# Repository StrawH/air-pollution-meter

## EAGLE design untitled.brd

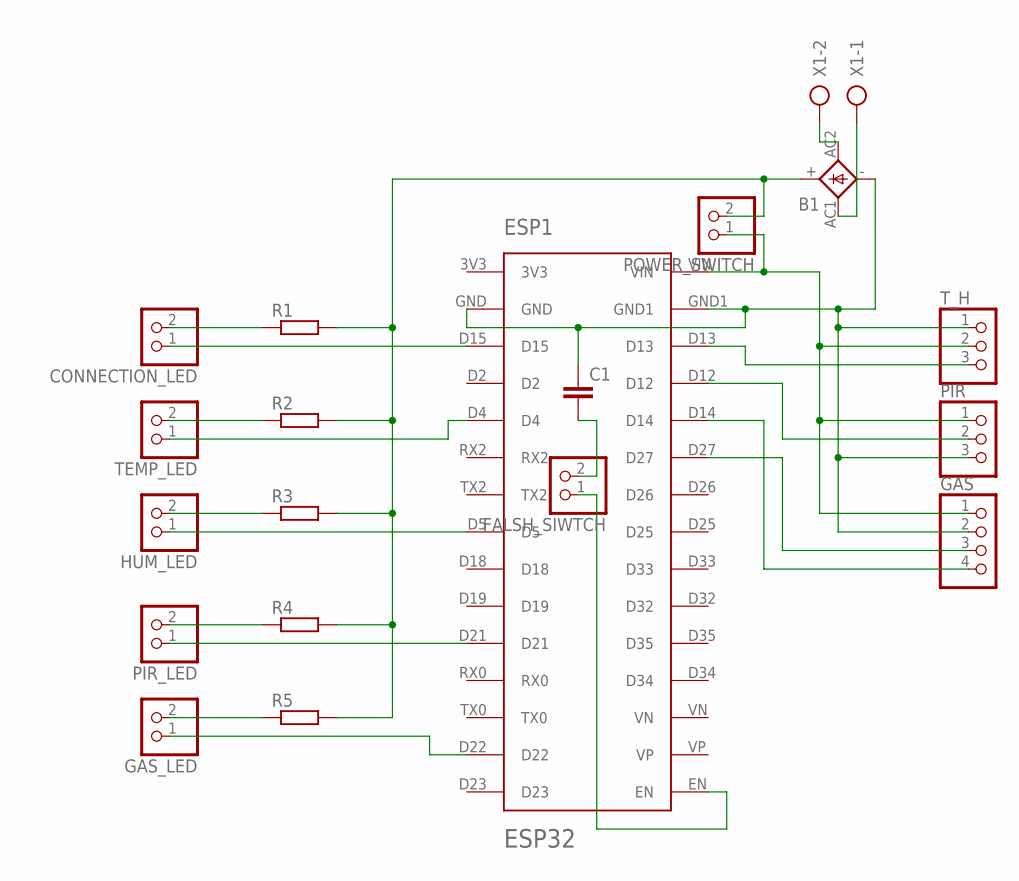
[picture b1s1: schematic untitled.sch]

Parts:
B1: 2KBB-R
C1: C5/2.5; C5B2.5
CONNECTION_LED: PINHD-1X2; 1X02
ESP1: ESP32; ESP-32
FALSH_SIWTCH: PINHD-1X2; 1X02
GAS: PINHD-1X4; 1X04
GAS_LED: PINHD-1X2; 1X02
HUM_LED: PINHD-1X2; 1X02
PIR: PINHD-1X3; 1X03
PIR_LED: PINHD-1X2; 1X02
POWER_SWITCH: PINHD-1X2; 1X02
R1, R2, R3, R4, R5: R-EU_0207/10; 0207/10
TEMP_LED: PINHD-1X2; 1X02
T_H: PINHD-1X3; 1X03
X1: AK300/2

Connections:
unnamed: B1.AC2, X1.2
unnamed: ESP1.D13, T_H.3
unnamed: ESP1.D12, PIR.2
unnamed: ESP1.D27, GAS.3
unnamed: ESP1.D14, GAS.4
unnamed: B1.-, C1.1, ESP1.GND, ESP1.GND1, GAS.2, PIR.3, T_H.1
unnamed: B1.AC1, X1.1
unnamed: B1.+, POWER_SWITCH.2, R1.2, R2.2, R3.2, R4.2, R5.2
unnamed: CONNECTION_LED.1, ESP1.D15
unnamed: ESP1.D4, TEMP_LED.1
unnamed: ESP1.D5, HUM_LED.1
unnamed: ESP1.D21, PIR_LED.1
unnamed: ESP1.D22, GAS_LED.1
unnamed: GAS_LED.2, R5.1
unnamed: PIR_LED.2, R4.1
unnamed: HUM_LED.2, R3.1
unnamed: R2.1, TEMP_LED.2
unnamed: CONNECTION_LED.2, R1.1
unnamed: ESP1.VIN, GAS.1, PIR.1, POWER_SWITCH.1, T_H.2
unnamed: C1.2, FALSH_SIWTCH.2
unnamed: ESP1.EN, FALSH_SIWTCH.1

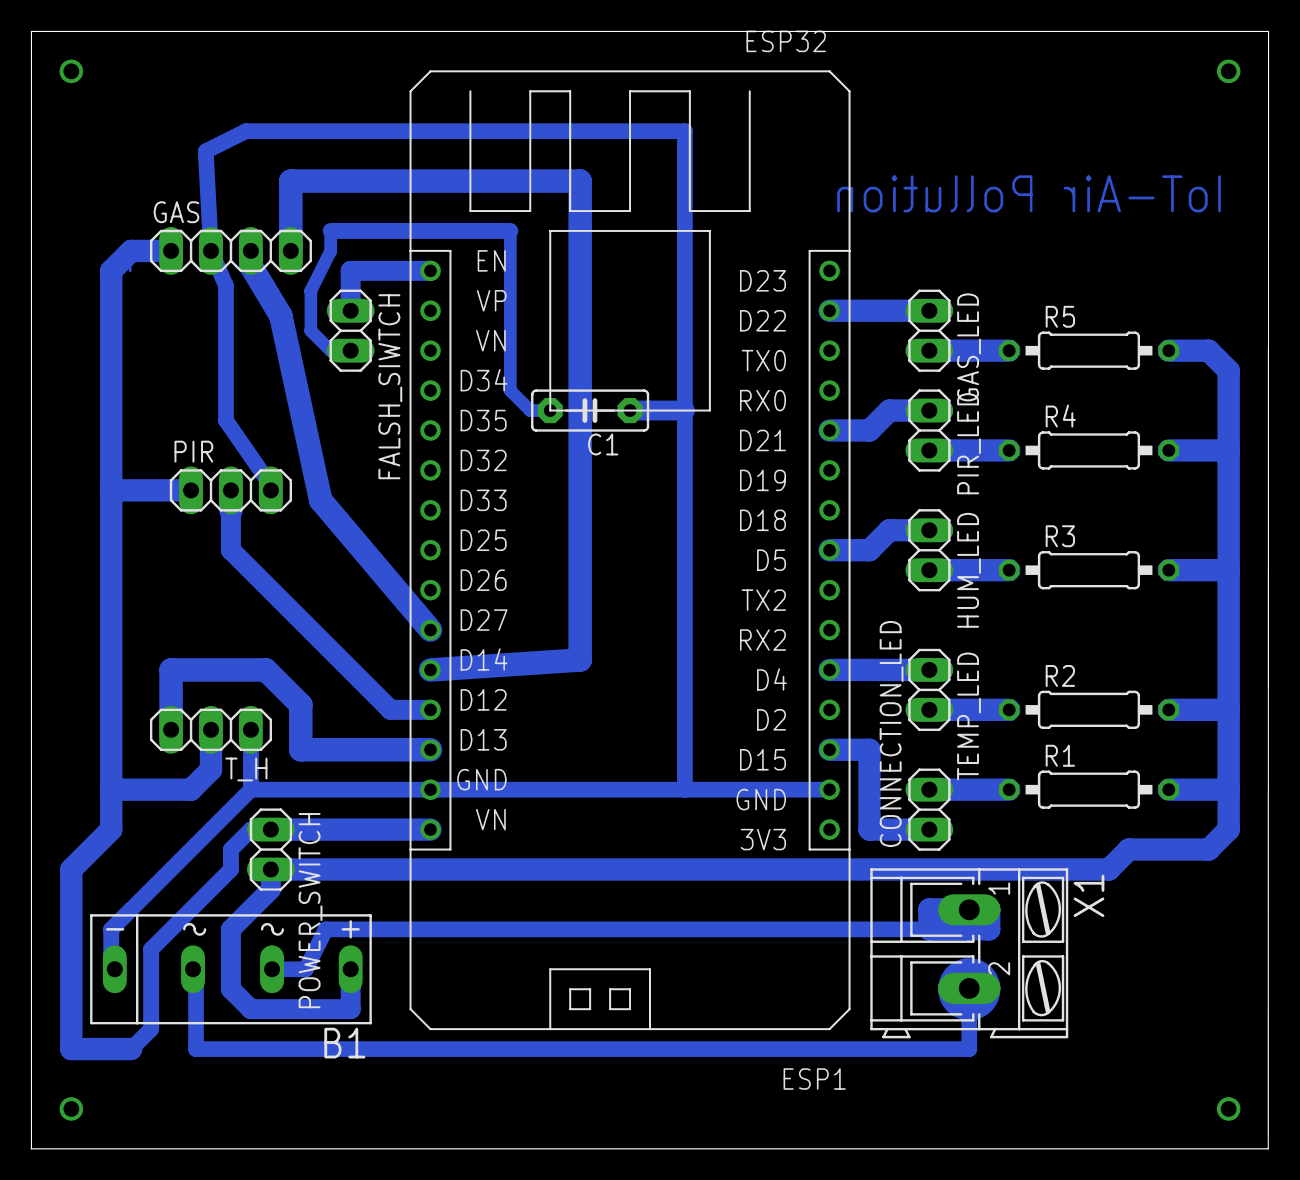
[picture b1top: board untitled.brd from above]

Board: 2 copper layers, 78.7 x 71.1 mm, 19 parts (0 on the bottom side), 21 nets.

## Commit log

2019-08-19 Create Main
